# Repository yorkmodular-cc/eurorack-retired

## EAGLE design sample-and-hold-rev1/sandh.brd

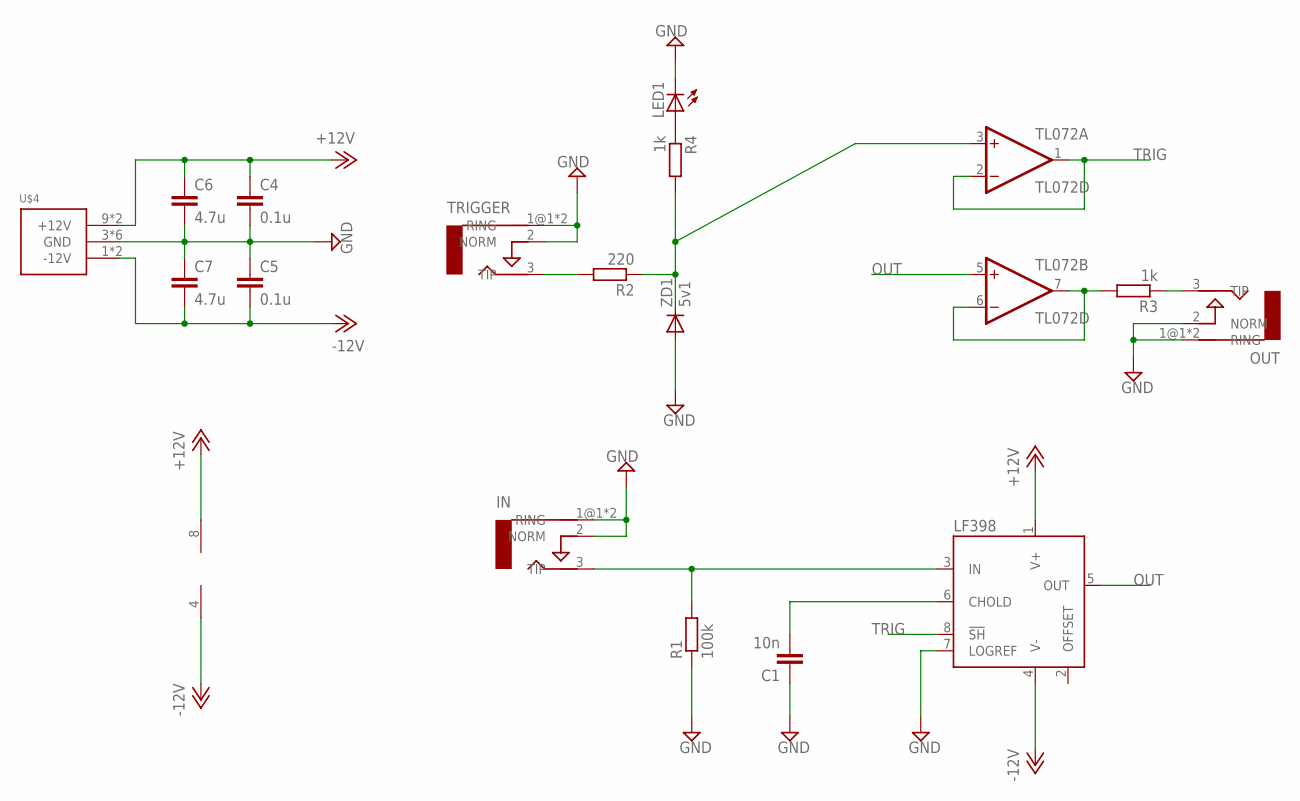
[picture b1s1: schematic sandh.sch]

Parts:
C1: 10n; C0805
C4, C5: 0.1u; C0805
C6, C7: 4.7u; C0805
IN: AUDIO-JACKERTHENVAR; ERTHENVAR-JACK
LED1: LEDCHIP-LED0805; CHIP-LED0805
LF398: LF398AD; SO08
OUT: AUDIO-JACKERTHENVAR; ERTHENVAR-JACK
R1: 100k; R0805
R2: 220; R0805
R3, R4: 1k; R0805
TL072: TL072D; SO08
TRIGGER: AUDIO-JACKERTHENVAR; ERTHENVAR-JACK
U$4: POWER_SIMPLE10; POWER_10
ZD1: 5v1; SOD323-W

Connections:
+12V: C4.1, C6.1, LF398.1 (V+), TL072.8 (V+), U$4.9 (+12V), U$4.10 (+12V)
-12V: C5.2, C7.2, LF398.4 (V-), TL072.4 (V-), U$4.1 (-12V), U$4.2 (-12V)
GND: C1.1, C4.2, C5.1, C6.2, C7.1, IN.1@1 (RING), IN.1@2 (RING), IN.2 (NORM), LED1.C, LF398.7 (LOGREF), OUT.1@1 (RING), OUT.1@2 (RING), OUT.2 (NORM), R1.1, TRIGGER.1@1 (RING), TRIGGER.1@2 (RING), TRIGGER.2 (NORM), U$4.3 (GND), U$4.4 (GND), U$4.5 (GND), U$4.6 (GND), U$4.7 (GND), U$4.8 (GND), ZD1.A
unnamed: IN.3 (TIP), LF398.3 (IN), R1.2
unnamed: C1.2, LF398.6 (CHOLD)
unnamed: LED1.A, R4.1
unnamed: R2.2, TRIGGER.3 (TIP)
unnamed: R3.2, TL072.6 (-IN), TL072.7 (OUT)
unnamed: OUT.3 (TIP), R3.1
OUT: LF398.5 (OUT), TL072.5 (+IN)
TRIG: LF398.8 (!SH), R2.1, R4.2, TL072.1 (OUT), TL072.2 (-IN), TL072.3 (+IN), ZD1.C

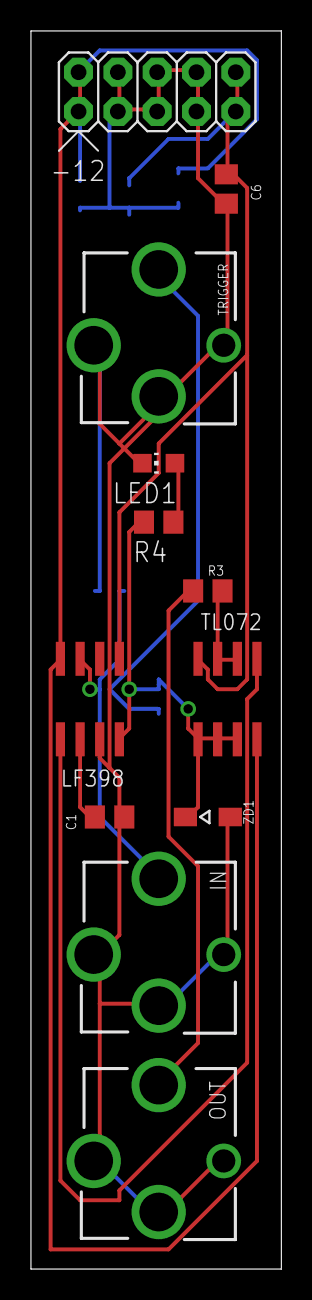
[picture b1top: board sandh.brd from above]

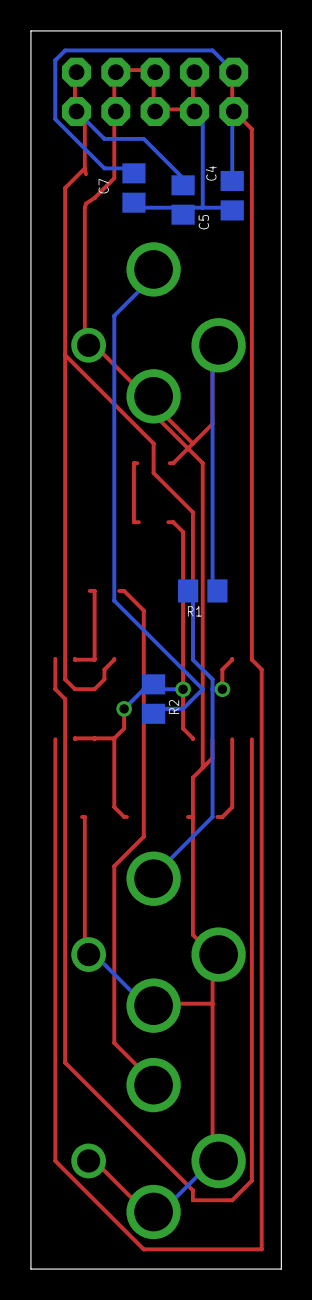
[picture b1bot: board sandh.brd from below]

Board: 2 copper layers, 16.2 x 80.0 mm, 17 parts (5 on the bottom side), 11 nets.

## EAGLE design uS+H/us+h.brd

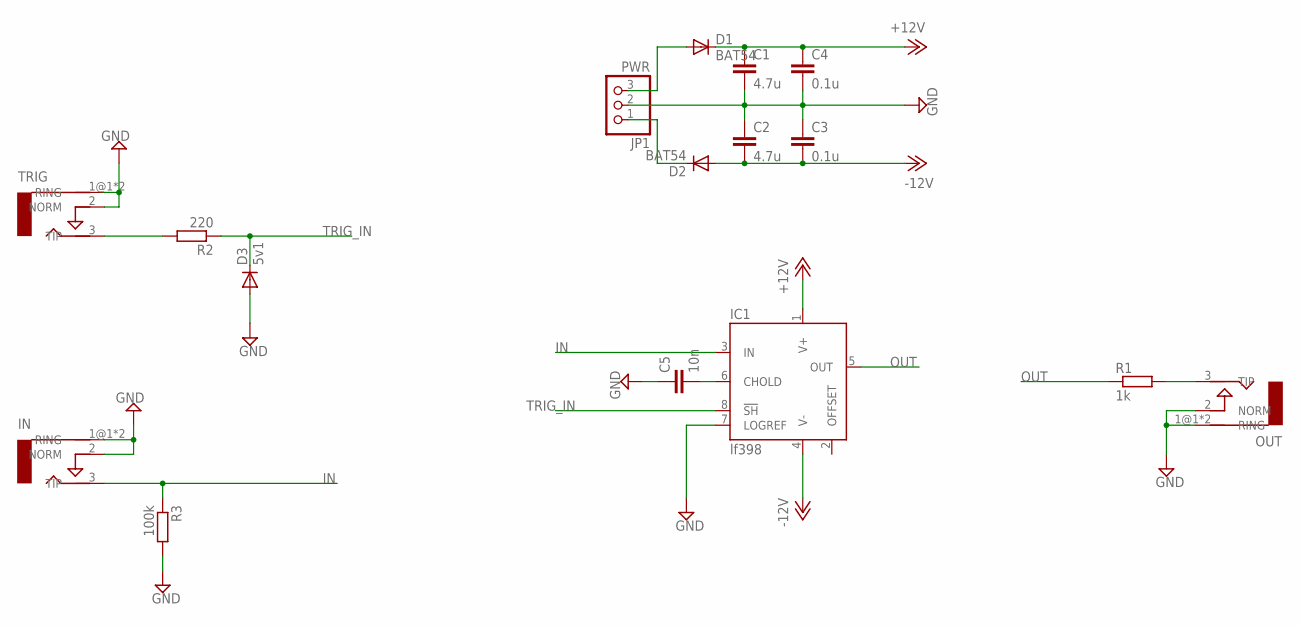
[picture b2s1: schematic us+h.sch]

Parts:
C1, C2: 4.7u; C0805
C3, C4: 0.1u; C0805
C5: 10n; C050-025X075
D1, D2: BAT54; SOD323-W
D3: 5v1; SOD323-W
IC1: lf398; SO08
IN: in; ERTHENVAR-JACK
JP1: PWR; 1X03
OUT: out; ERTHENVAR-JACK
R1: 1k; R0805
R2: 220; R0805
R3: 100k; R0805
TRIG: trig; ERTHENVAR-JACK

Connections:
+12: D1.A, JP1.3
+12V: C1.1, C4.1, D1.C, IC1.1 (V+)
-12: D2.C, JP1.1
-12V: C2.2, C3.2, D2.A, IC1.4 (V-)
GND: C1.2, C2.1, C3.1, C4.2, C5.1, D3.A, IC1.7 (LOGREF), IN.1@1 (RING), IN.1@2 (RING), IN.2 (NORM), JP1.2, OUT.1@1 (RING), OUT.1@2 (RING), OUT.2 (NORM), R3.2, TRIG.1@1 (RING), TRIG.1@2 (RING), TRIG.2 (NORM)
IN: IC1.3 (IN), IN.3 (TIP), R3.1
unnamed: C5.2, IC1.6 (CHOLD)
unnamed: R2.2, TRIG.3 (TIP)
unnamed: OUT.3 (TIP), R1.2
OUT: IC1.5 (OUT), R1.1
TRIG_IN: D3.C, IC1.8 (!SH), R2.1

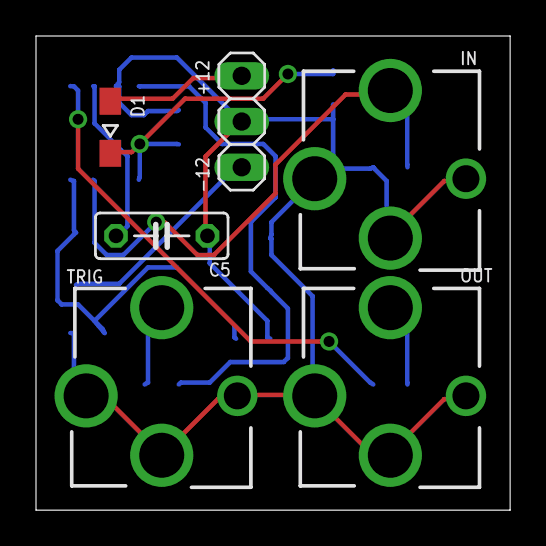
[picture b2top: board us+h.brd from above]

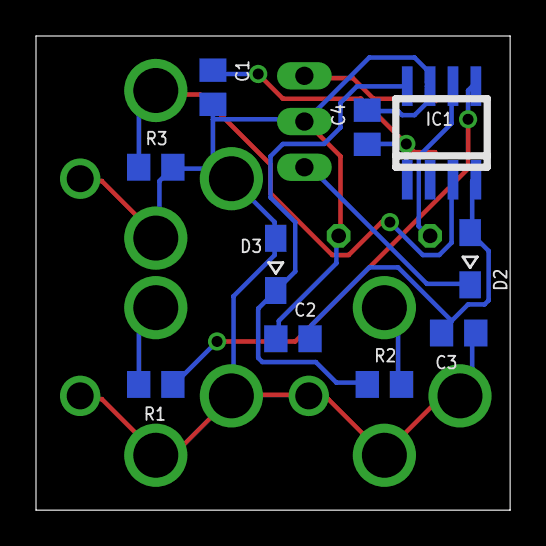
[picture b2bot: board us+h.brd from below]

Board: 2 copper layers, 26.3 x 26.3 mm, 16 parts (10 on the bottom side), 11 nets.

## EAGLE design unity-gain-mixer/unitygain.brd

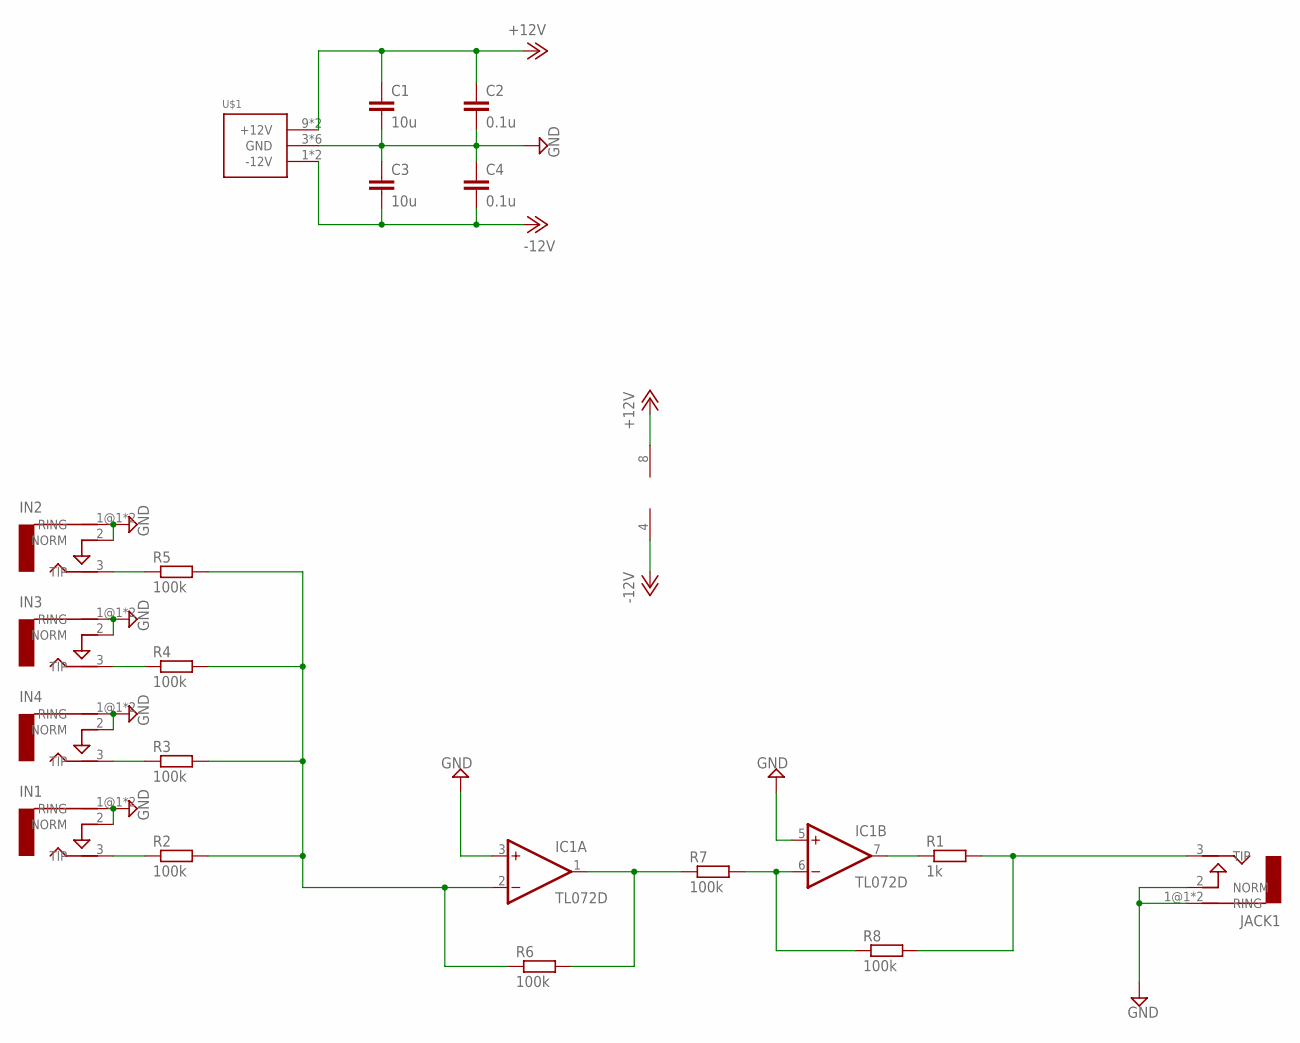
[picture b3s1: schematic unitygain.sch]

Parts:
C1, C3: 10u; C0805
C2, C4: 0.1u; C0805
IC1: TL072D; SO08
IN1: IN1; ERTHENVAR-JACK
IN2: IN2; ERTHENVAR-JACK
IN3: IN3; ERTHENVAR-JACK
IN4: IN4; ERTHENVAR-JACK
JACK1: OUT; ERTHENVAR-JACK
R1: 1k; R0805
R2, R3, R4, R5, R6, R7, R8: 100k; R0805
U$1: POWER_SIMPLE10; POWER_10

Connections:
+12V: C1.1, C2.1, IC1.8 (V+), U$1.9 (+12V), U$1.10 (+12V)
-12V: C3.2, C4.2, IC1.4 (V-), U$1.1 (-12V), U$1.2 (-12V)
GND: C1.2, C2.2, C3.1, C4.1, IC1.3 (+IN), IC1.5 (+IN), IN1.1@1 (RING), IN1.1@2 (RING), IN1.2 (NORM), IN2.1@1 (RING), IN2.1@2 (RING), IN2.2 (NORM), IN3.1@1 (RING), IN3.1@2 (RING), IN3.2 (NORM), IN4.1@1 (RING), IN4.1@2 (RING), IN4.2 (NORM), JACK1.1@1 (RING), JACK1.1@2 (RING), JACK1.2 (NORM), U$1.3 (GND), U$1.4 (GND), U$1.5 (GND), U$1.6 (GND), U$1.7 (GND), U$1.8 (GND)
unnamed: JACK1.3 (TIP), R1.2, R8.2
unnamed: IC1.7 (OUT), R1.1
unnamed: IN1.3 (TIP), R2.1
unnamed: IC1.6 (-IN), R7.2, R8.1
unnamed: IC1.2 (-IN), R2.2, R3.2, R4.2, R5.2, R6.1
unnamed: IN4.3 (TIP), R3.1
unnamed: IN3.3 (TIP), R4.1
unnamed: IN2.3 (TIP), R5.1
unnamed: IC1.1 (OUT), R6.2, R7.1

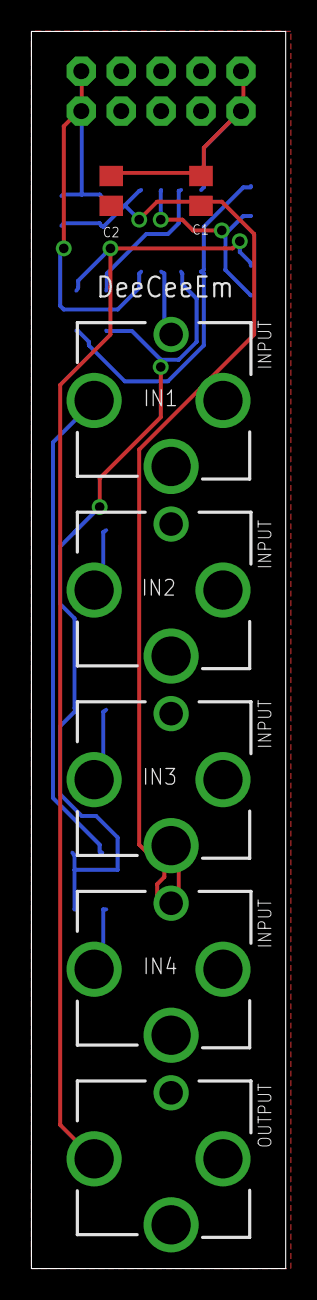
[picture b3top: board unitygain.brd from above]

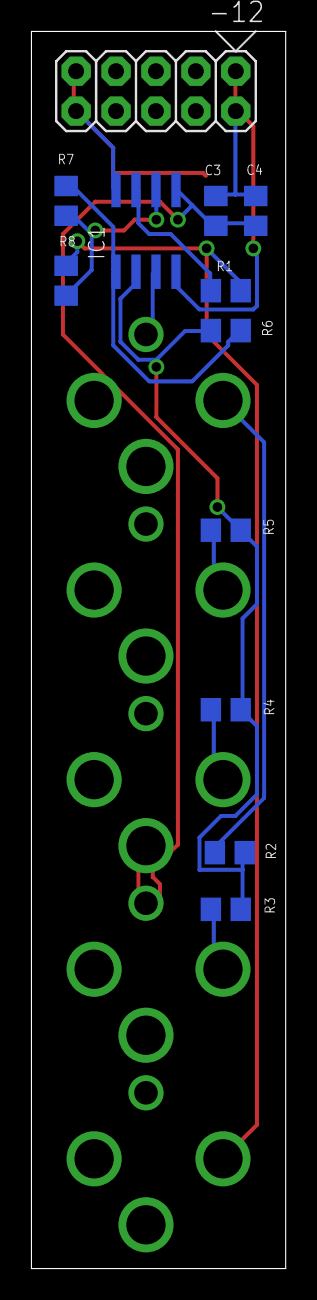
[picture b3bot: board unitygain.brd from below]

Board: 2 copper layers, 16.2 x 78.7 mm, 19 parts (12 on the bottom side), 12 nets.

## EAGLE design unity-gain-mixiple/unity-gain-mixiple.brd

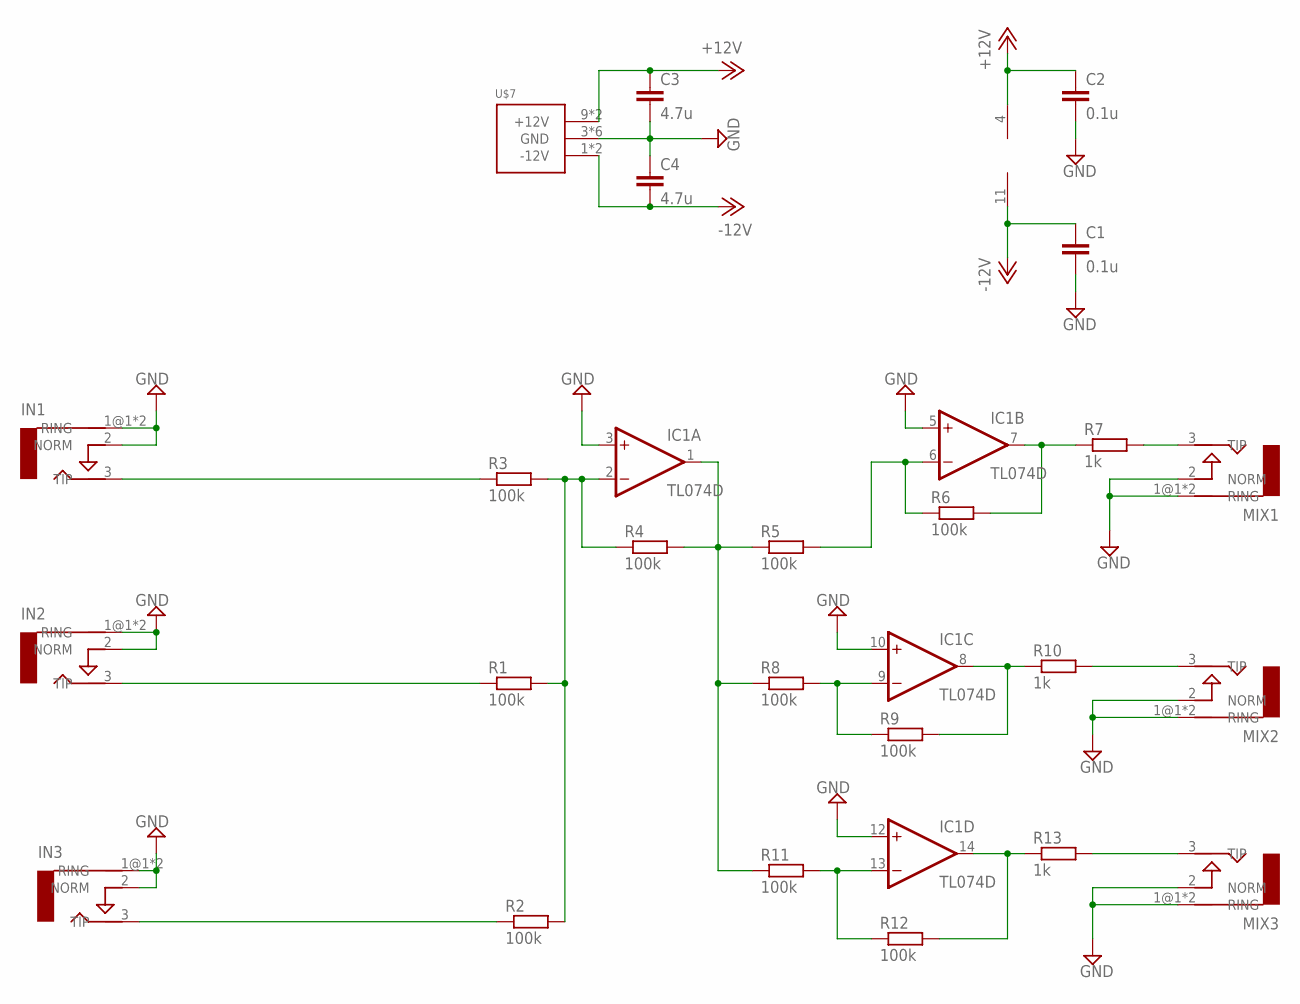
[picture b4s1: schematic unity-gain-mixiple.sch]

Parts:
C1, C2: 0.1u; C0805
C3, C4: 4.7u; C0805
IC1: TL074D; SO14
IN1, IN2, IN3: AUDIO-JACKERTHENVAR; ERTHENVAR-JACK
MIX1, MIX2, MIX3: AUDIO-JACKERTHENVAR; ERTHENVAR-JACK
R1, R2, R3, R4, R5, R6, R8, R9, R11, R12: 100k; R0805
R7, R10, R13: 1k; R0805
U$7: POWER_SIMPLE10; POWER_10

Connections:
+12V: C2.1, C3.1, IC1.4 (V+), U$7.9 (+12V), U$7.10 (+12V)
-12V: C1.1, C4.2, IC1.11 (V-), U$7.1 (-12V), U$7.2 (-12V)
GND: C1.2, C2.2, C3.2, C4.1, IC1.3 (+IN), IC1.5 (+IN), IC1.10 (+IN), IC1.12 (+IN), IN1.1@1 (RING), IN1.1@2 (RING), IN1.2 (NORM), IN2.1@1 (RING), IN2.1@2 (RING), IN2.2 (NORM), IN3.1@1 (RING), IN3.1@2 (RING), IN3.2 (NORM), MIX1.1@1 (RING), MIX1.1@2 (RING), MIX1.2 (NORM), MIX2.1@1 (RING), MIX2.1@2 (RING), MIX2.2 (NORM), MIX3.1@1 (RING), MIX3.1@2 (RING), MIX3.2 (NORM), U$7.3 (GND), U$7.4 (GND), U$7.5 (GND), U$7.6 (GND), U$7.7 (GND), U$7.8 (GND)
unnamed: IC1.7 (OUT), R6.2, R7.1
unnamed: IC1.8 (OUT), R9.2, R10.1
unnamed: IC1.14 (OUT), R12.2, R13.1
unnamed: IC1.6 (-IN), R5.2, R6.1
unnamed: IC1.9 (-IN), R8.2, R9.1
unnamed: IC1.13 (-IN), R11.2, R12.1
unnamed: IN1.3 (TIP), R3.1
unnamed: IC1.2 (-IN), R1.2, R2.2, R3.2, R4.1
unnamed: IN2.3 (TIP), R1.1
unnamed: IN3.3 (TIP), R2.1
unnamed: IC1.1 (OUT), R4.2, R5.1, R8.1, R11.1
unnamed: MIX2.3 (TIP), R10.2
unnamed: MIX3.3 (TIP), R13.2
unnamed: MIX1.3 (TIP), R7.2

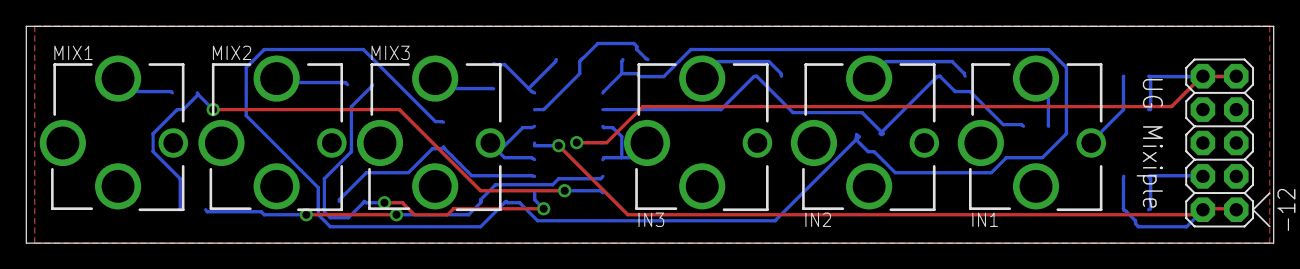
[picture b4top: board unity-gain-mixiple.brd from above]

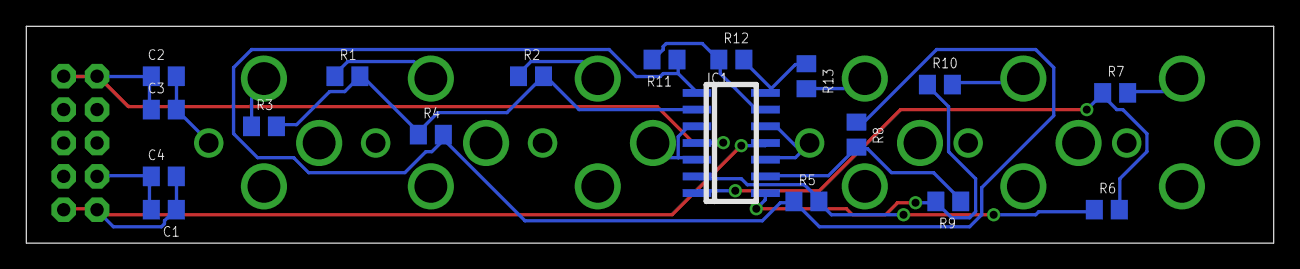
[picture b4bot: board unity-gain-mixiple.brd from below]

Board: 2 copper layers, 94.9 x 16.5 mm, 25 parts (18 on the bottom side), 17 nets.

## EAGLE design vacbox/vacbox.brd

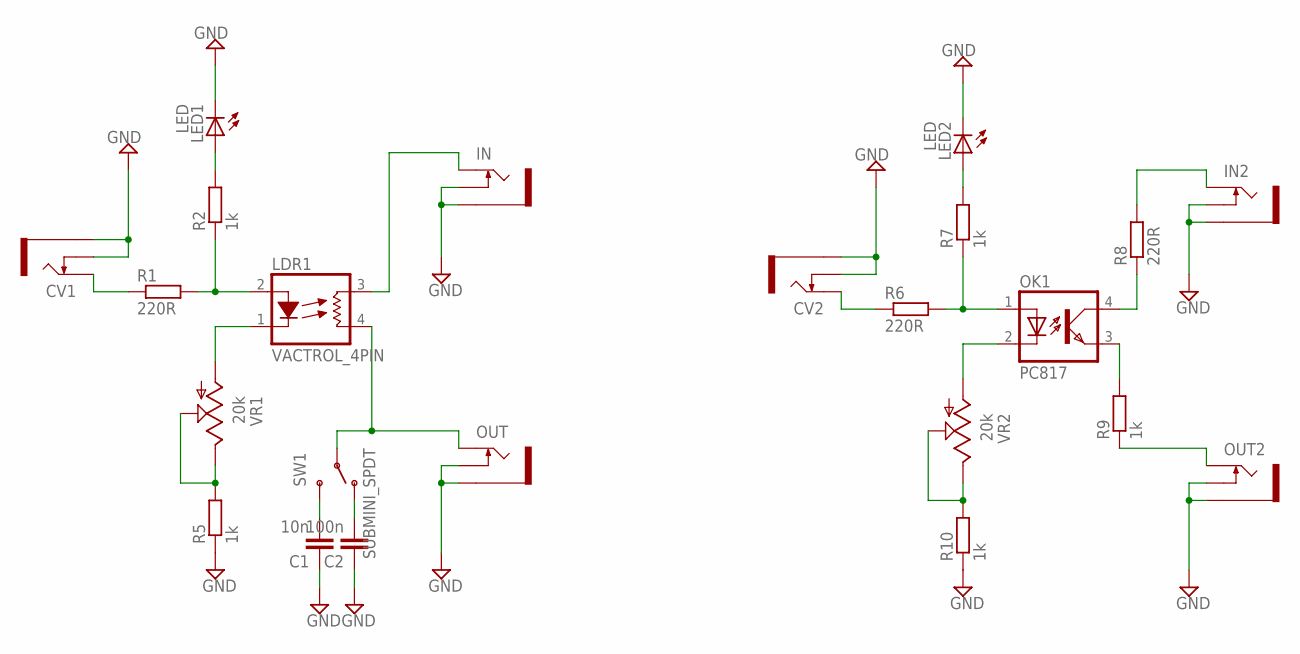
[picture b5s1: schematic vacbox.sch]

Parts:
C1: 10n; C050-025X075
C2: 100n; C050-025X075
CV1, CV2: PJ302M
IN, IN2: PJ302M
LDR1: VACTROL_4PIN; VACTROL_4PIN_VTL5C
LED1, LED2: LED; LED3MM
OK1: PC817; DIL04
OUT, OUT2: PJ302M
R1, R6, R8: 220R; 0207/2V
R2, R5, R7, R9, R10: 1k; 0207/2V
SW1: SUBMINI_SPDT; SUBMINI_TOGGLE
VR1, VR2: 20k; 9MM_SNAP-IN_POT

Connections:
CV2: CV2.TIP, R6.1
CV_IN: LDR1.2 (LED+), R1.2, R2.1
CV_IN1: OK1.1 (A), R6.2, R7.1
CV_OUT: LDR1.1 (LED-), VR1.1 (A)
CV_OUT1: OK1.2 (C), VR2.1 (A)
GND: C1.1, C2.1, CV1.GND (SLEEVE), CV1.SW (SWITCH), CV2.GND (SLEEVE), CV2.SW (SWITCH), IN.GND (SLEEVE), IN.SW (SWITCH), IN2.GND (SLEEVE), IN2.SW (SWITCH), LED1.K (C), LED2.K (C), OUT.GND (SLEEVE), OUT.SW (SWITCH), OUT2.GND (SLEEVE), OUT2.SW (SWITCH), R5.1, R10.1
unnamed: R5.2, VR1.2 (S), VR1.3 (E)
unnamed: OUT2.TIP, R9.1
unnamed: OK1.4 (COL), R8.1
unnamed: LED2.A, R7.2
unnamed: C1.2, SW1.3 (S)
unnamed: R10.2, VR2.2 (S), VR2.3 (E)
unnamed: C2.2, SW1.1 (O)
unnamed: CV1.TIP, R1.1
unnamed: LED1.A, R2.2
SIG_IN: IN.TIP, LDR1.3 (RES1)
SIG_IN1: IN2.TIP, R8.2
SIG_OUT: LDR1.4 (RES2), OUT.TIP, SW1.COM (COMMON)
SIG_OUT1: OK1.3 (EMIT), R9.2

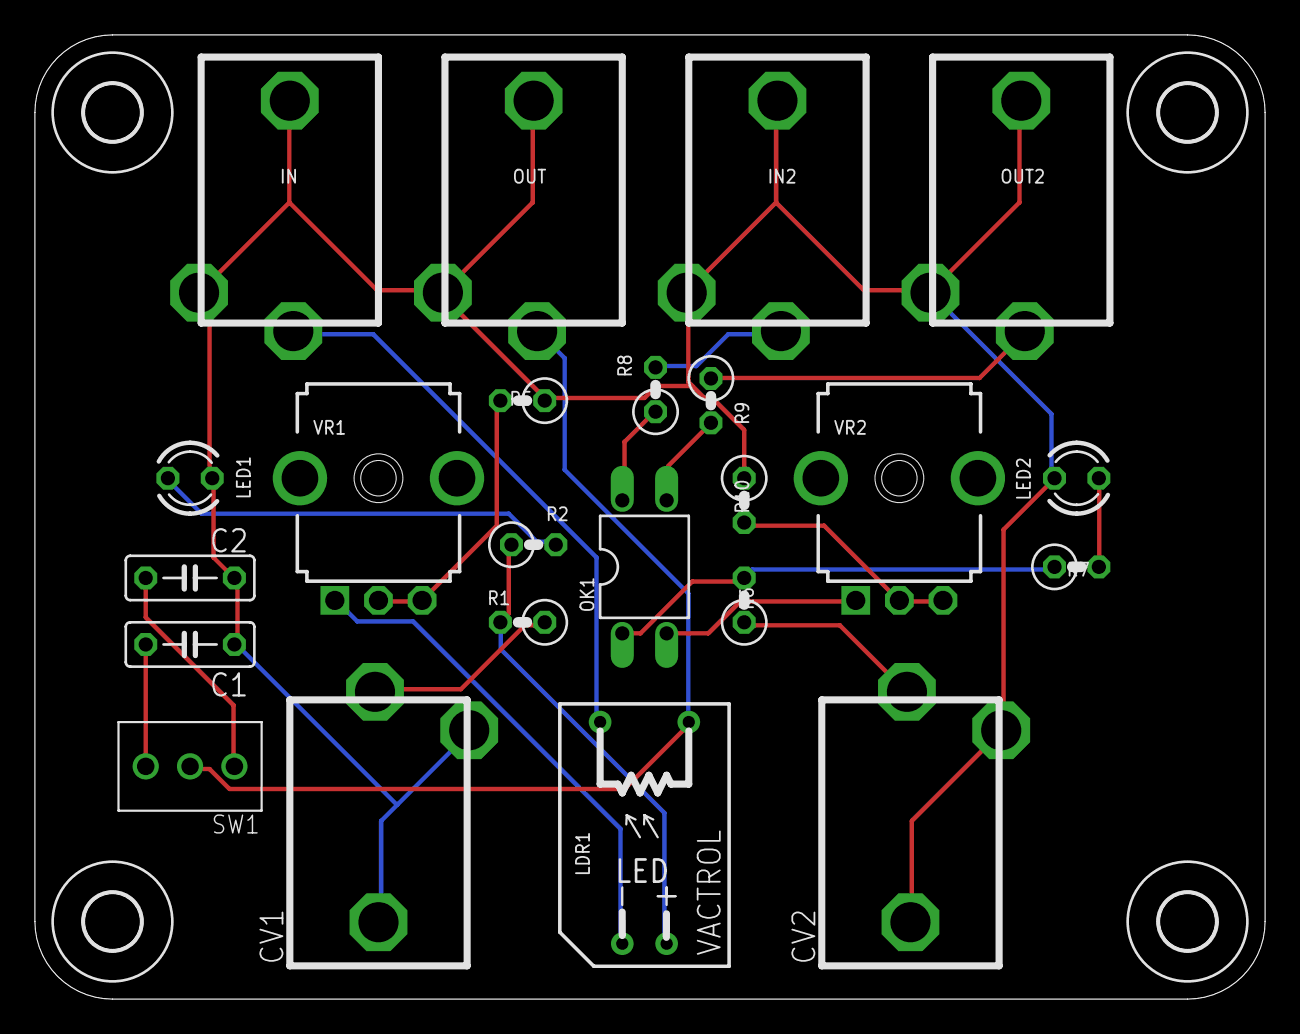
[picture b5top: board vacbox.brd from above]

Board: 2 copper layers, 70.5 x 55.2 mm, 27 parts (0 on the bottom side), 19 nets.

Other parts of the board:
U$1, U$2, U$3, U$4: 3,2

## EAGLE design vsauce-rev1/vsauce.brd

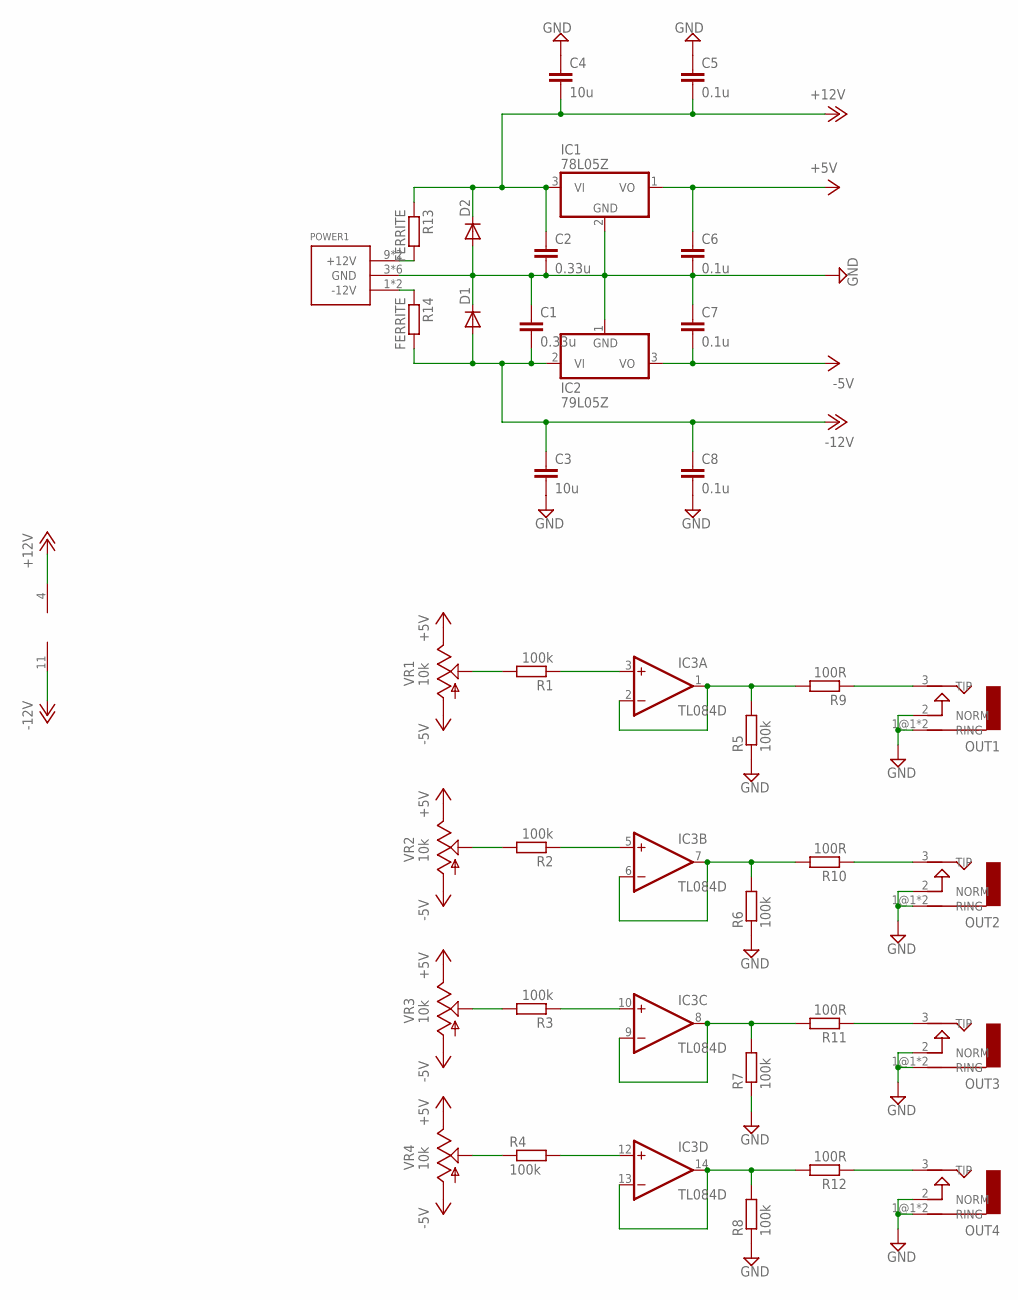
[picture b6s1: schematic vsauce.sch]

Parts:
C1, C2: 0.33u; C0805
C3, C4: 10u; C0805
C5, C6, C7, C8: 0.1u; C0805
D1, D2: DIODE-SOD323-W; SOD323-W
IC1: 78L05Z; TO92
IC2: 79L05Z; TO92
IC3: TL084D; SO14
OUT1: V1; ERTHENVAR-JACK
OUT2: V2; ERTHENVAR-JACK
OUT3: V3; ERTHENVAR-JACK
OUT4: V4; ERTHENVAR-JACK
POWER1: POWER_SIMPLE10; POWER_10
R1, R2, R3, R4, R5, R6, R7, R8: 100k; R0805
R9, R10, R11, R12: 100R; R0805
R13, R14: FERRITE; R0805
VR1, VR2, VR3, VR4: 10k; 9MM_SNAP-IN_POT

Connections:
+5V: C6.1, IC1.1 (VO), VR1.3 (E), VR2.3 (E), VR3.3 (E), VR4.3 (E)
+12V: C2.1, C4.2, C5.2, D2.C, IC1.3 (VI), IC3.4 (V+), R13.1
-5V: C7.2, IC2.3 (VO), VR1.1 (A), VR2.1 (A), VR3.1 (A), VR4.1 (A)
-12V: C1.2, C3.1, C8.1, D1.A, IC2.2 (VI), IC3.11 (V-), R14.2
GND: C1.1, C2.2, C3.2, C4.1, C5.1, C6.2, C7.1, C8.2, D1.C, D2.A, IC1.2 (GND), IC2.1 (GND), OUT1.1@1 (RING), OUT1.1@2 (RING), OUT1.2 (NORM), OUT2.1@1 (RING), OUT2.1@2 (RING), OUT2.2 (NORM), OUT3.1@1 (RING), OUT3.1@2 (RING), OUT3.2 (NORM), OUT4.1@1 (RING), OUT4.1@2 (RING), OUT4.2 (NORM), POWER1.3 (GND), POWER1.4 (GND), POWER1.5 (GND), POWER1.6 (GND), POWER1.7 (GND), POWER1.8 (GND), R5.1, R6.1, R7.1, R8.1
unnamed: IC3.1 (OUT), IC3.2 (-IN), R5.2, R9.2
unnamed: IC3.6 (-IN), IC3.7 (OUT), R6.2, R10.2
unnamed: IC3.8 (OUT), IC3.9 (-IN), R7.2, R11.2
unnamed: IC3.13 (-IN), IC3.14 (OUT), R8.2, R12.2
unnamed: IC3.3 (+IN), R1.1
unnamed: IC3.5 (+IN), R2.1
unnamed: IC3.10 (+IN), R3.1
unnamed: IC3.12 (+IN), R4.2
unnamed: R3.2, VR3.2 (S)
unnamed: R4.1, VR4.2 (S)
unnamed: R2.2, VR2.2 (S)
unnamed: R1.2, VR1.2 (S)
unnamed: OUT1.3 (TIP), R9.1
unnamed: OUT2.3 (TIP), R10.1
unnamed: OUT3.3 (TIP), R11.1
unnamed: OUT4.3 (TIP), R12.1
unnamed: POWER1.9 (+12V), POWER1.10 (+12V), R13.2
unnamed: POWER1.1 (-12V), POWER1.2 (-12V), R14.1

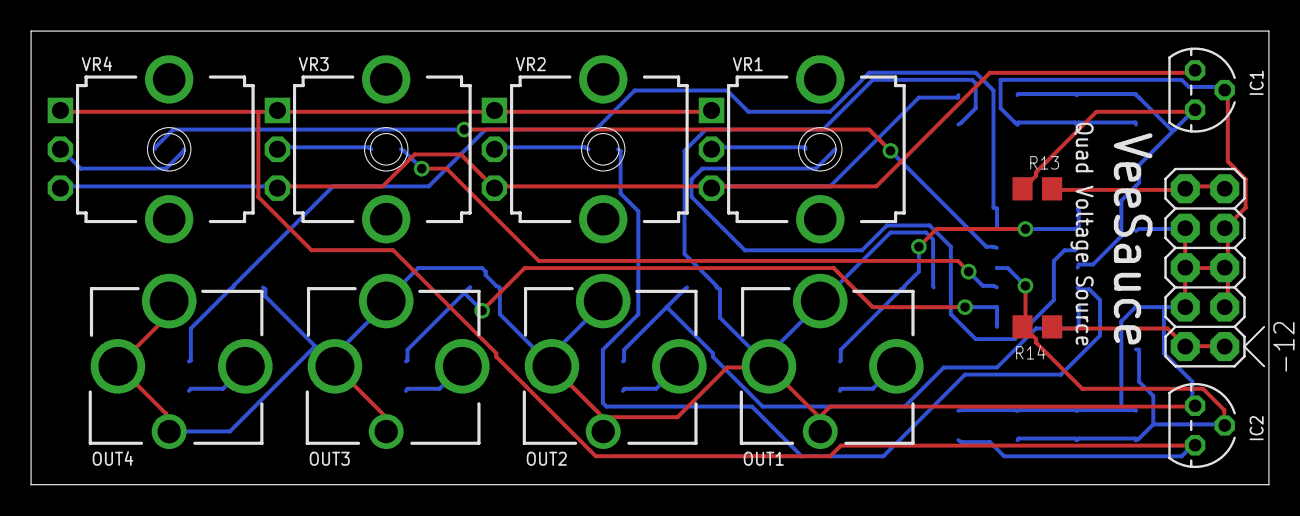
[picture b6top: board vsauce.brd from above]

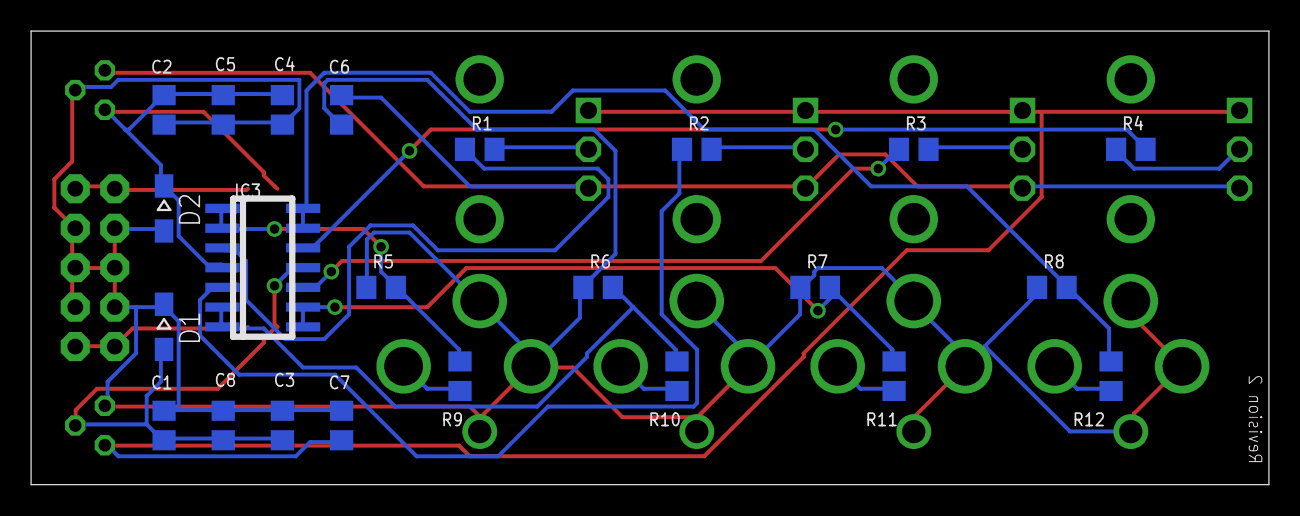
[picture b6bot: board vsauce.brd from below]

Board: 2 copper layers, 79.7 x 29.2 mm, 36 parts (23 on the bottom side), 23 nets.

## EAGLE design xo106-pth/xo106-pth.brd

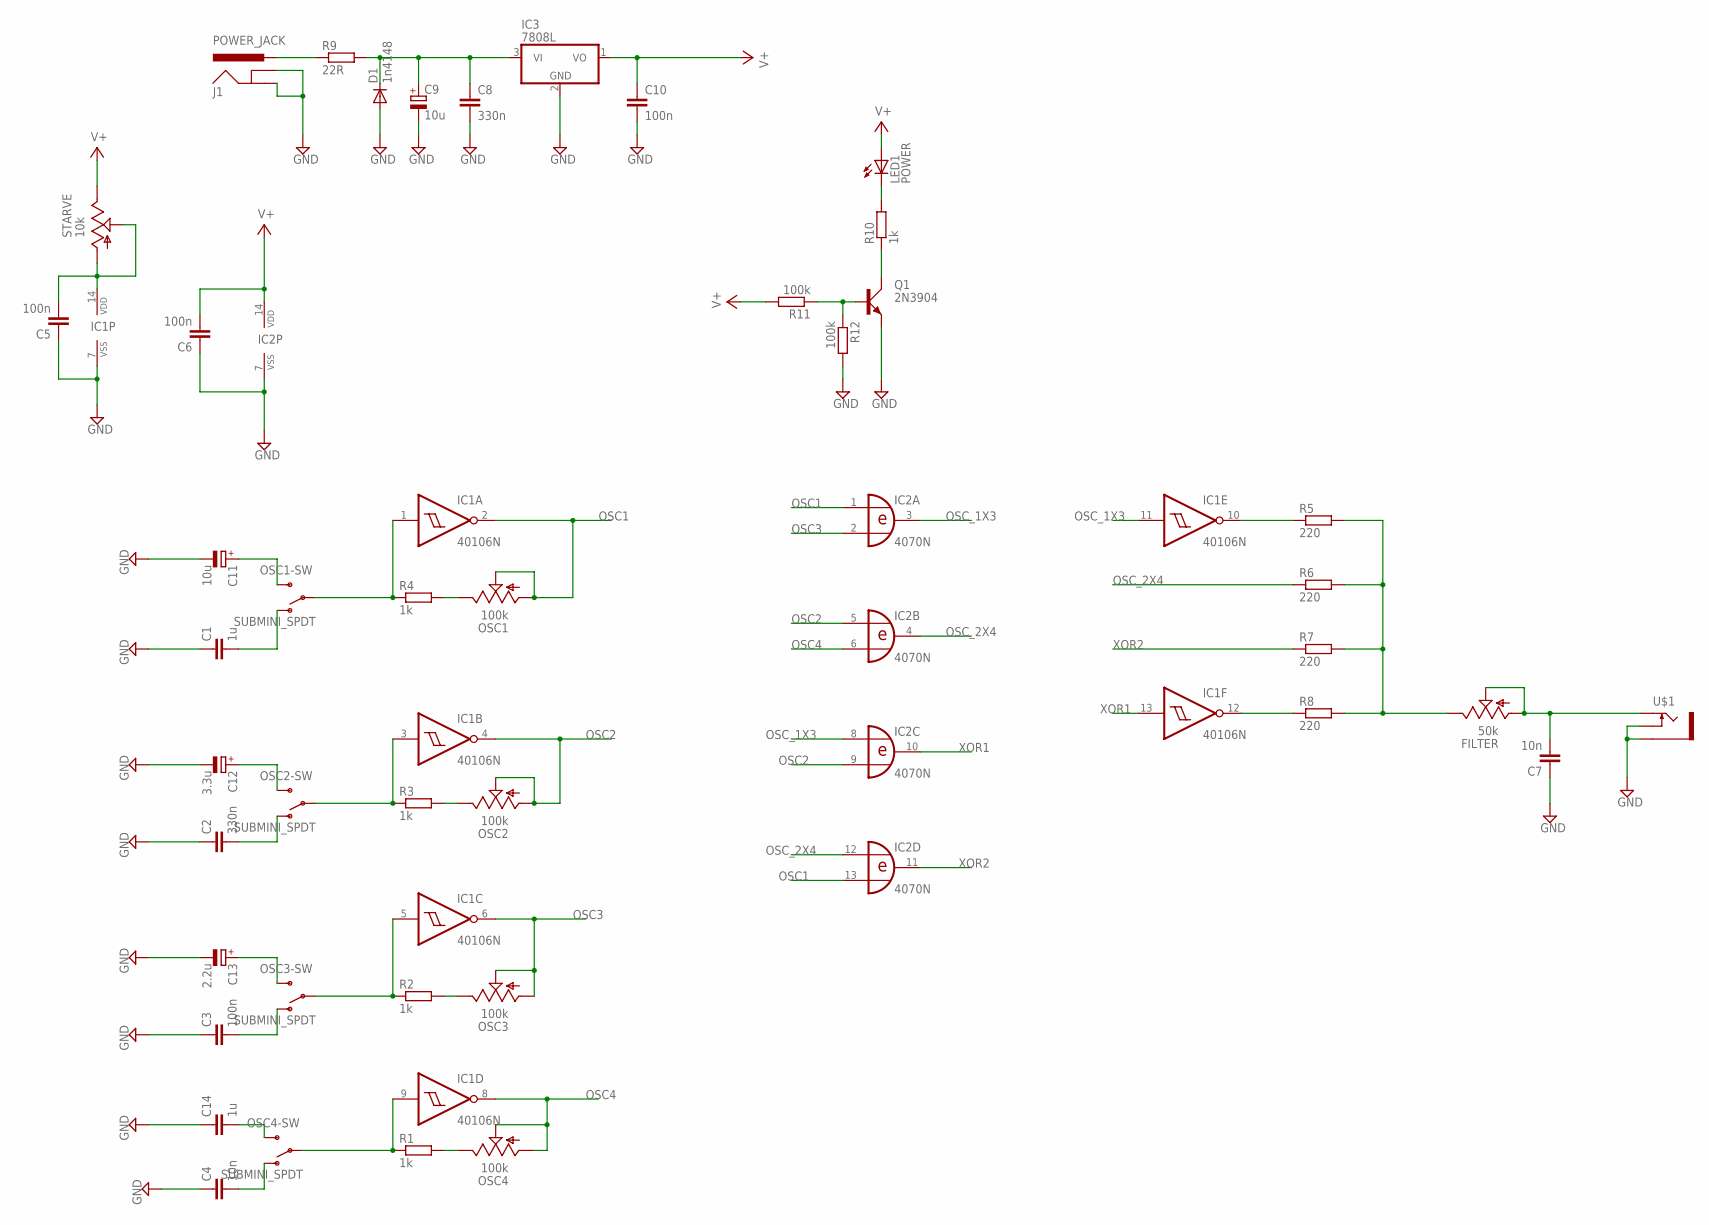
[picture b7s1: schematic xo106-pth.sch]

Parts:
C1, C14: 1u; C050-025X075
C2: 330n; C050-025X075
C3: 100n; C050-025X075
C4, C7: 10n; C050-025X075
C5, C6, C10: 100n; C025-025X050
C8: 330n; C025-025X050
C9, C11: 10u; E2,5-5
C12: 3.3u; E2,5-5
C13: 2.2u; E2,5-5
D1: 1n4148; D-2.5
FILTER: 50k; 9MM_SNAP-IN_POT
IC1: 40106N; DIL14
IC2: 4070N; DIL14
IC3: 7808L; TO92
J1: POWER_JACK; POWER_JACK_PTH
LED1: POWER; LED3MM
OSC1, OSC2, OSC3, OSC4: 100k; 9MM_SNAP-IN_POT
OSC1-SW, OSC2-SW, OSC3-SW, OSC4-SW: SUBMINI_SPDT; SUBMINI_TOGGLE
Q1: 2N3904; TO92D
R1, R2, R3, R4, R10: 1k; 0207/2V
R5, R6, R7, R8: 220; 0207/2V
R9: 22R; 0207/2V
R11, R12: 100k; 0207/2V
STARVE: 10k; 9MM_SNAP-IN_POT
U$1: PJ302M

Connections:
GND: C1.1, C2.1, C3.1, C4.1, C5.1, C6.1, C7.1, C8.2, C9.-, C10.2, C11.-, C12.-, C13.-, C14.1, D1.A, IC1.7 (VSS), IC2.7 (VSS), IC3.2 (GND), J1.GND, J1.GNDBREAK, Q1.E, R12.2, U$1.GND (SLEEVE), U$1.SW (SWITCH)
unnamed: IC1.3 (I), OSC2-SW.COM (COMMON), R3.1
unnamed: IC1.5 (I), OSC3-SW.COM (COMMON), R2.1
unnamed: IC1.1 (I), OSC1-SW.COM (COMMON), R4.1
unnamed: OSC1.3 (E), R4.2
unnamed: FILTER.3 (E), R5.2, R6.2, R7.2, R8.2
unnamed: OSC2.3 (E), R3.2
unnamed: C7.2, FILTER.1 (A), FILTER.2 (S), U$1.TIP
unnamed: IC1.10 (O), R5.1
unnamed: OSC3.3 (E), R2.2
unnamed: IC1.9 (I), OSC4-SW.COM (COMMON), R1.1
unnamed: OSC4.3 (E), R1.2
unnamed: IC1.12 (O), R8.1
unnamed: C5.2, IC1.14 (VDD), STARVE.1 (A), STARVE.2 (S)
unnamed: C8.1, C9.+, D1.C, IC3.3 (VI), R9.2
unnamed: C11.+, OSC1-SW.3 (S)
unnamed: C1.2, OSC1-SW.1 (O)
unnamed: Q1.B, R11.1, R12.1
unnamed: Q1.C, R10.1
unnamed: C12.+, OSC2-SW.3 (S)
unnamed: J1.PWR, R9.1
unnamed: C2.2, OSC2-SW.1 (O)
unnamed: LED1.K (C), R10.2
unnamed: C13.+, OSC3-SW.3 (S)
unnamed: C3.2, OSC3-SW.1 (O)
unnamed: C4.2, OSC4-SW.1 (O)
unnamed: C14.2, OSC4-SW.3 (S)
OSC1: IC1.2 (O), IC2.1 (I0), IC2.13 (I1), OSC1.1 (A), OSC1.2 (S)
OSC2: IC1.4 (O), IC2.5 (I0), IC2.9 (I1), OSC2.1 (A), OSC2.2 (S)
OSC3: IC1.6 (O), IC2.2 (I1), OSC3.1 (A), OSC3.2 (S)
OSC4: IC1.8 (O), IC2.6 (I1), OSC4.1 (A), OSC4.2 (S)
OSC_1X3: IC1.11 (I), IC2.3 (O), IC2.8 (I0)
OSC_2X4: IC2.4 (O), IC2.12 (I0), R6.1
V+: C6.2, C10.1, IC2.14 (VDD), IC3.1 (VO), LED1.A, R11.2, STARVE.3 (E)
XOR1: IC1.13 (I), IC2.10 (O)
XOR2: IC2.11 (O), R7.1

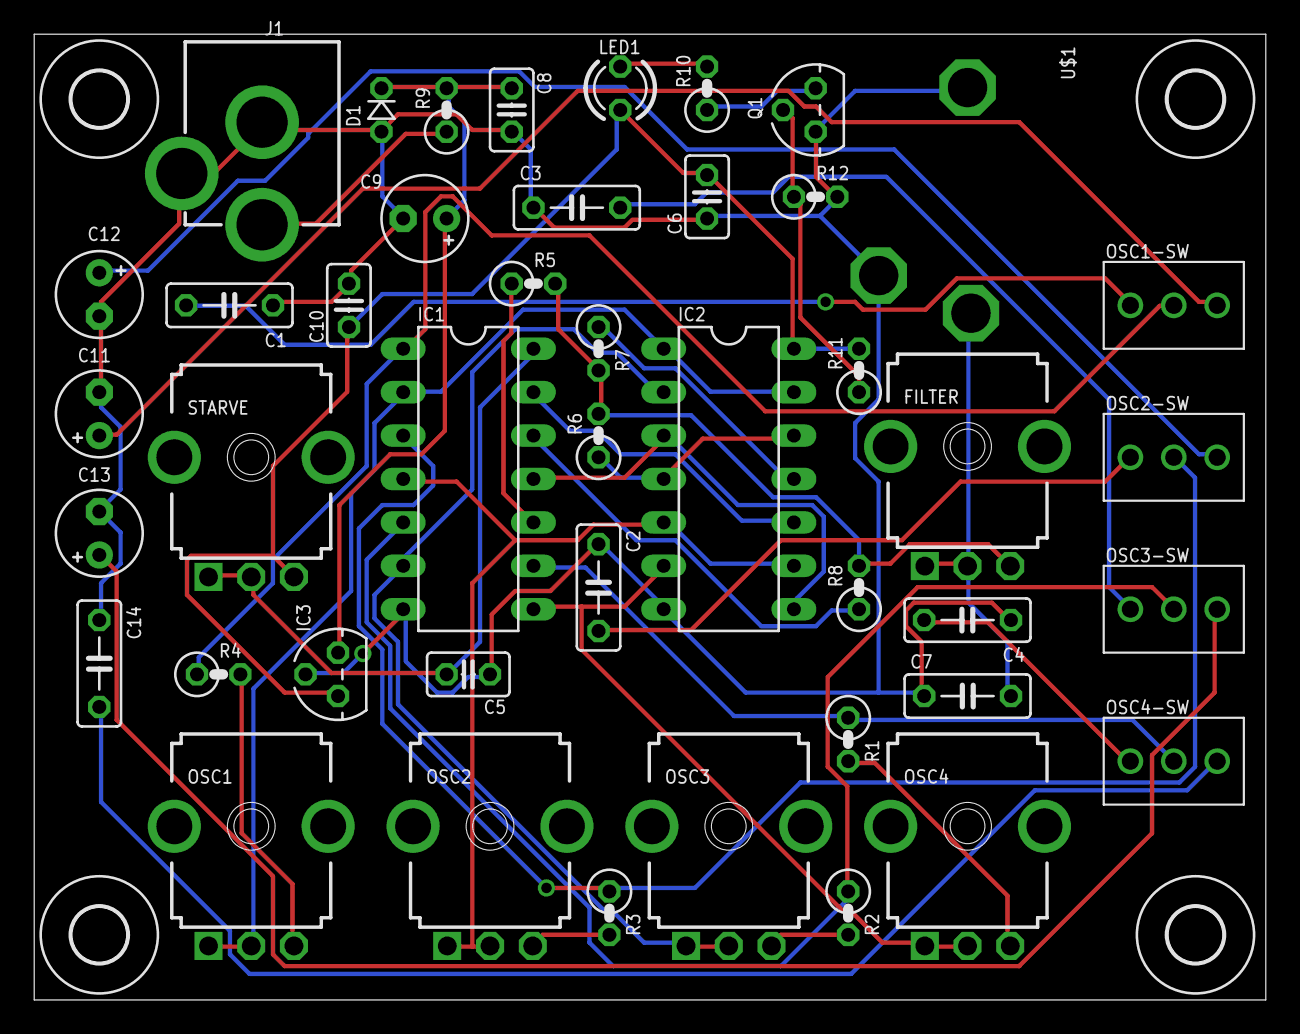
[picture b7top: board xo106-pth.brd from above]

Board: 2 copper layers, 72.1 x 56.5 mm, 48 parts (0 on the bottom side), 36 nets.

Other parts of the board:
U$6, U$7, U$8, U$9: 3,2

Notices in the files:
parts and their libraries:
SparkFun-Connectors: Licensing: Creative Commons ShareAlike 4.0 International - https://creativecommons.org/licenses/by-sa/4.0
